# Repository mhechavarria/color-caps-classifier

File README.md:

# color-caps-classifier
A project made mostly in python to classifie color caps using OpenCV and Python

Link to video: https://drive.google.com/open?id=1r29vyWqCW7NpwiLaEyCusYoAQh5E9Sr1

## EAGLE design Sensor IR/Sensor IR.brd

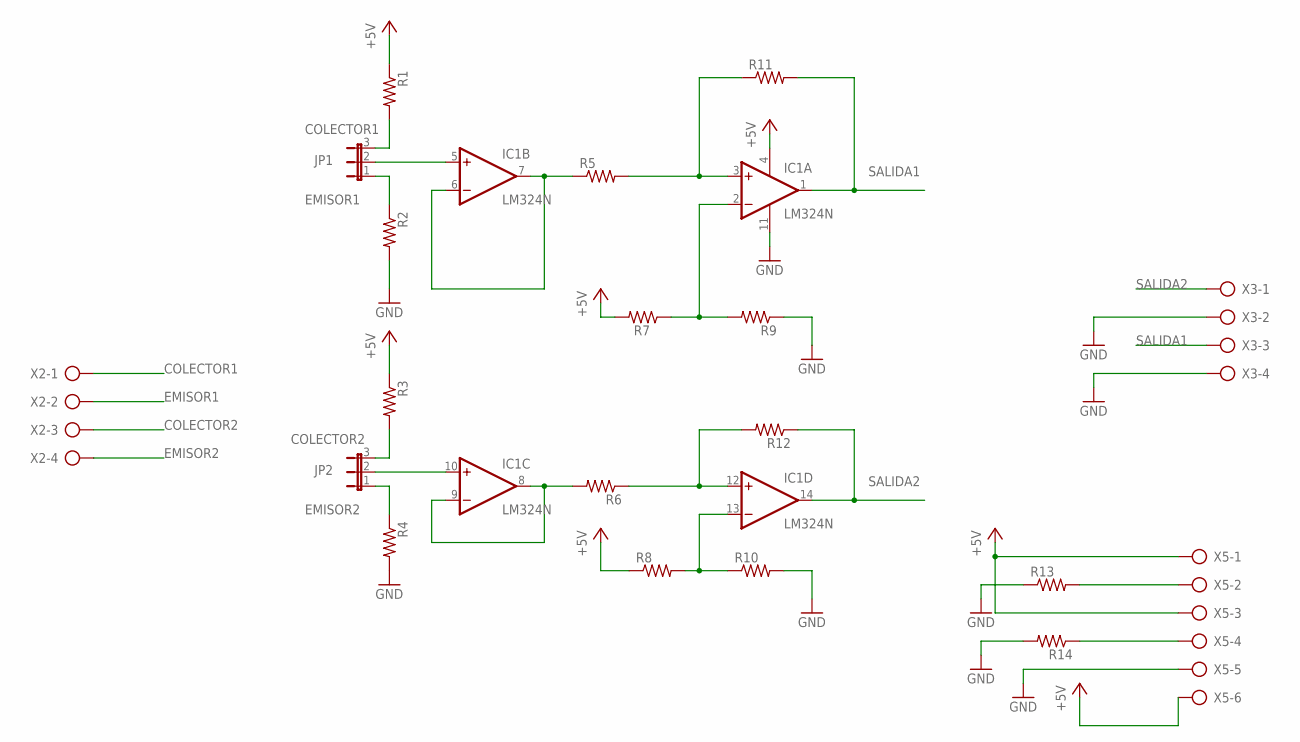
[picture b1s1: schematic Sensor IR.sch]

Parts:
IC1: LM324N; DIL14
JP1, JP2: JP2E; JP2
R1, R2, R3, R4, R5, R6, R7, R8, R9, R10, R11, R12, R13, R14: R-US_0207/10; 0207/10
X2, X3: AK500/4-H
X5: AK500/6-H

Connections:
+5V: IC1.4 (V+), R1.1, R3.1, R7.2, R8.1, X5.1, X5.3, X5.6
COLECTOR1: JP1.3, R1.2, X2.1
COLECTOR2: JP2.3, R3.2, X2.3
EMISOR1: JP1.1, R2.1, X2.2
EMISOR2: JP2.1, R4.1, X2.4
GND: IC1.11 (V-), R2.2, R4.2, R9.1, R10.2, R13.1, R14.2, X3.2, X3.4, X5.5
unnamed: IC1.6 (-IN), IC1.7 (OUT), R5.1
unnamed: IC1.8 (OUT), IC1.9 (-IN), R6.2
unnamed: IC1.3 (+IN), R5.2, R11.1
unnamed: R14.1, X5.4
unnamed: R13.2, X5.2
unnamed: IC1.5 (+IN), JP1.2
unnamed: IC1.13 (-IN), R8.2, R10.1
unnamed: IC1.12 (+IN), R6.1, R12.2
unnamed: IC1.2 (-IN), R7.1, R9.2
unnamed: IC1.10 (+IN), JP2.2
SALIDA1: IC1.1 (OUT), R11.2, X3.3
SALIDA2: IC1.14 (OUT), R12.1, X3.1

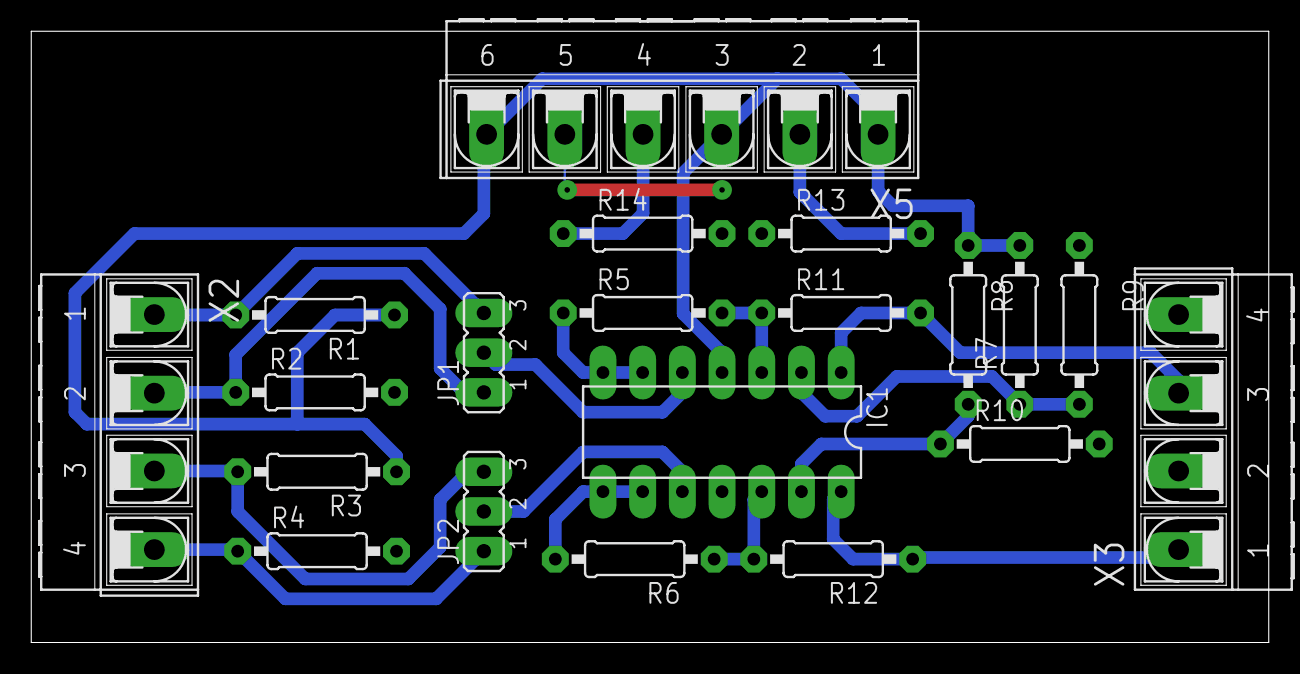
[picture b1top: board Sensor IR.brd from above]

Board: 2 copper layers, 79.2 x 39.1 mm, 20 parts (0 on the bottom side), 18 nets.

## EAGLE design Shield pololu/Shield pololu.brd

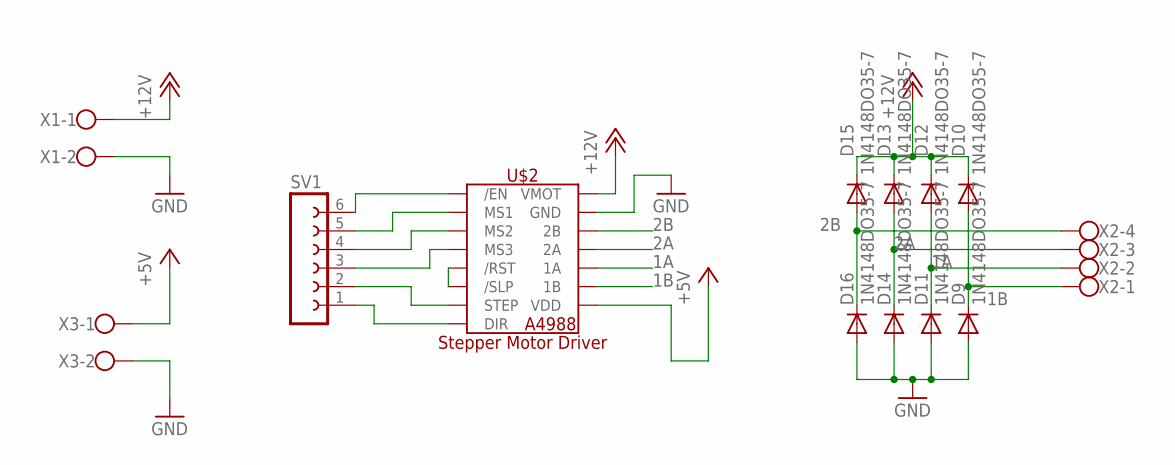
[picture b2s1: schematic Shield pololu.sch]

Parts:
D9, D10, D11, D12, D13, D14, D15, D16: 1N4148DO35-7; DO35-7
SV1: FE06-1; FE06
U$2: A4988_STEP
X1, X3: W237-102
X2: W237-4

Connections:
1A: D11.C, D12.A, U$2.1A, X2.2
1B: D9.C, D10.A, U$2.1B, X2.1
2A: D13.A, D14.C, U$2.2A, X2.3
2B: D15.A, D16.C, U$2.2B, X2.4
+5V: U$2.VDD, X3.1
+12V: D10.C, D12.C, D13.C, D15.C, U$2.VMOT, X1.1
GND: D9.A, D11.A, D14.A, D16.A, U$2.GND, U$2.GND2 (GND), X1.2, X3.2
unnamed: SV1.6, U$2./EN
unnamed: SV1.5, U$2.MS1
unnamed: SV1.4, U$2.MS2
unnamed: SV1.3, U$2.MS3
unnamed: SV1.2, U$2.STEP
unnamed: SV1.1, U$2.DIR
unnamed: U$2./RST, U$2./SLP

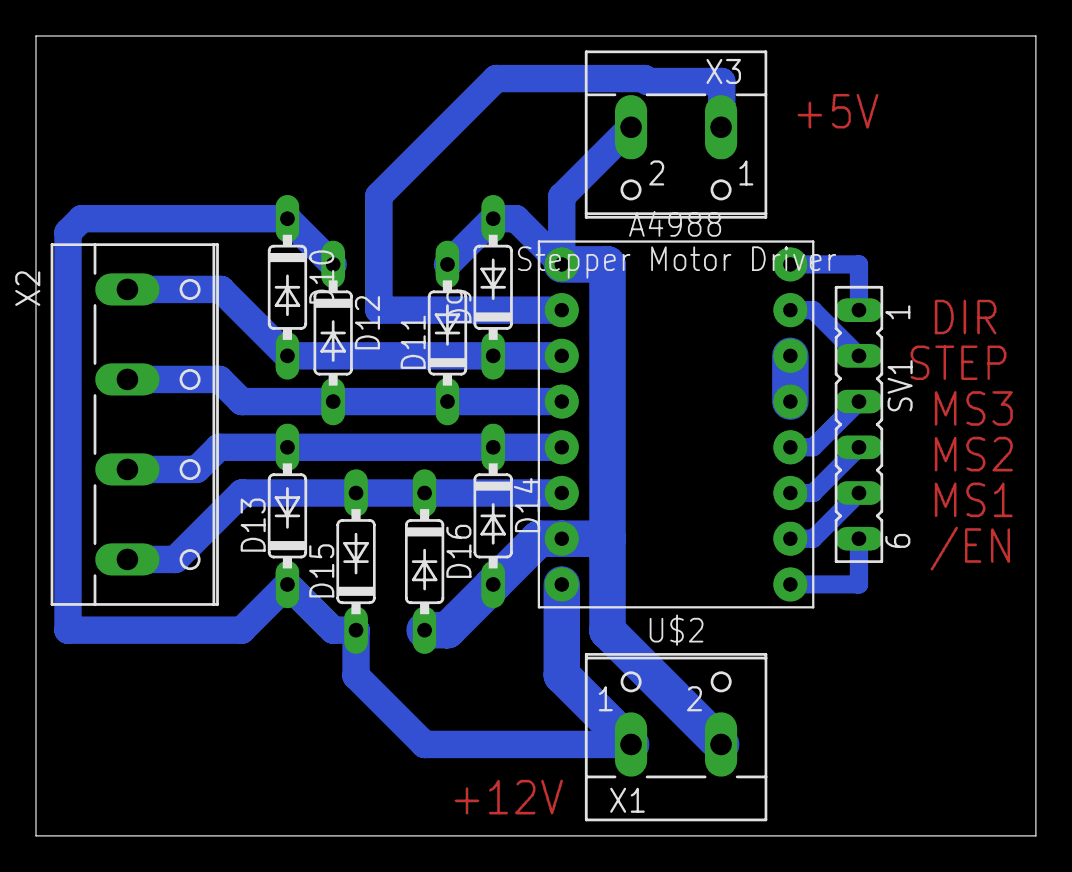
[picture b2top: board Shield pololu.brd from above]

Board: 2 copper layers, 55.5 x 44.4 mm, 13 parts (0 on the bottom side), 14 nets.
